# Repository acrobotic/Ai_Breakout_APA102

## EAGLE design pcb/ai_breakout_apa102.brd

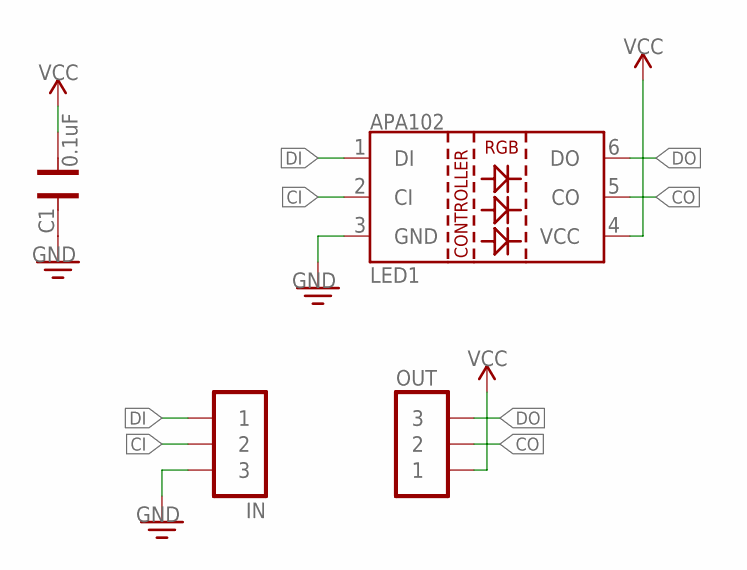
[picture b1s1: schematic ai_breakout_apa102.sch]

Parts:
C1: 0.1uF; CAP-0402
IN: 1X03
LED1: LED-APA102
OUT: 1X03NOFIRST; 1X03-NOFIRST

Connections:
CI: IN.2, LED1.2 (CI)
CO: LED1.5 (CO), OUT.2
DI: IN.1, LED1.1 (DI)
DO: LED1.6 (DO), OUT.3
GND: C1.2, IN.3, LED1.3 (GND)
VCC: C1.1, LED1.4 (VCC), OUT.1

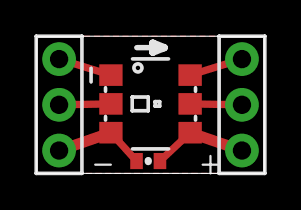
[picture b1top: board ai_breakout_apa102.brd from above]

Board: 2 copper layers, 12.7 x 7.6 mm, 5 parts (1 on the bottom side), 6 nets.

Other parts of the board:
U$5: AI-LOGO-XS

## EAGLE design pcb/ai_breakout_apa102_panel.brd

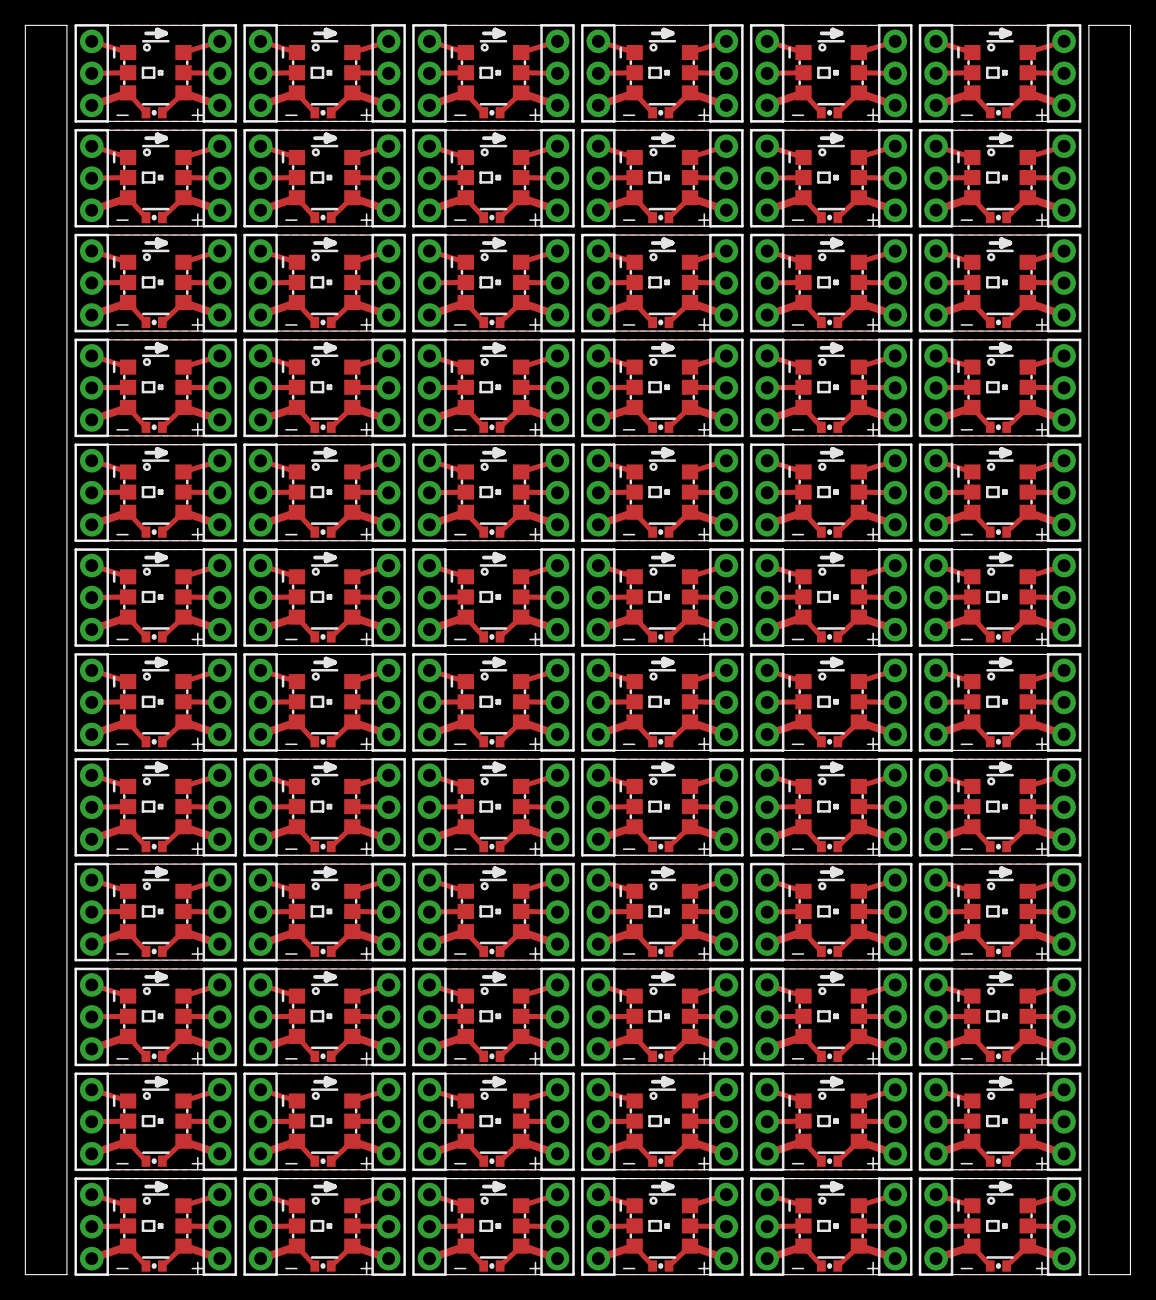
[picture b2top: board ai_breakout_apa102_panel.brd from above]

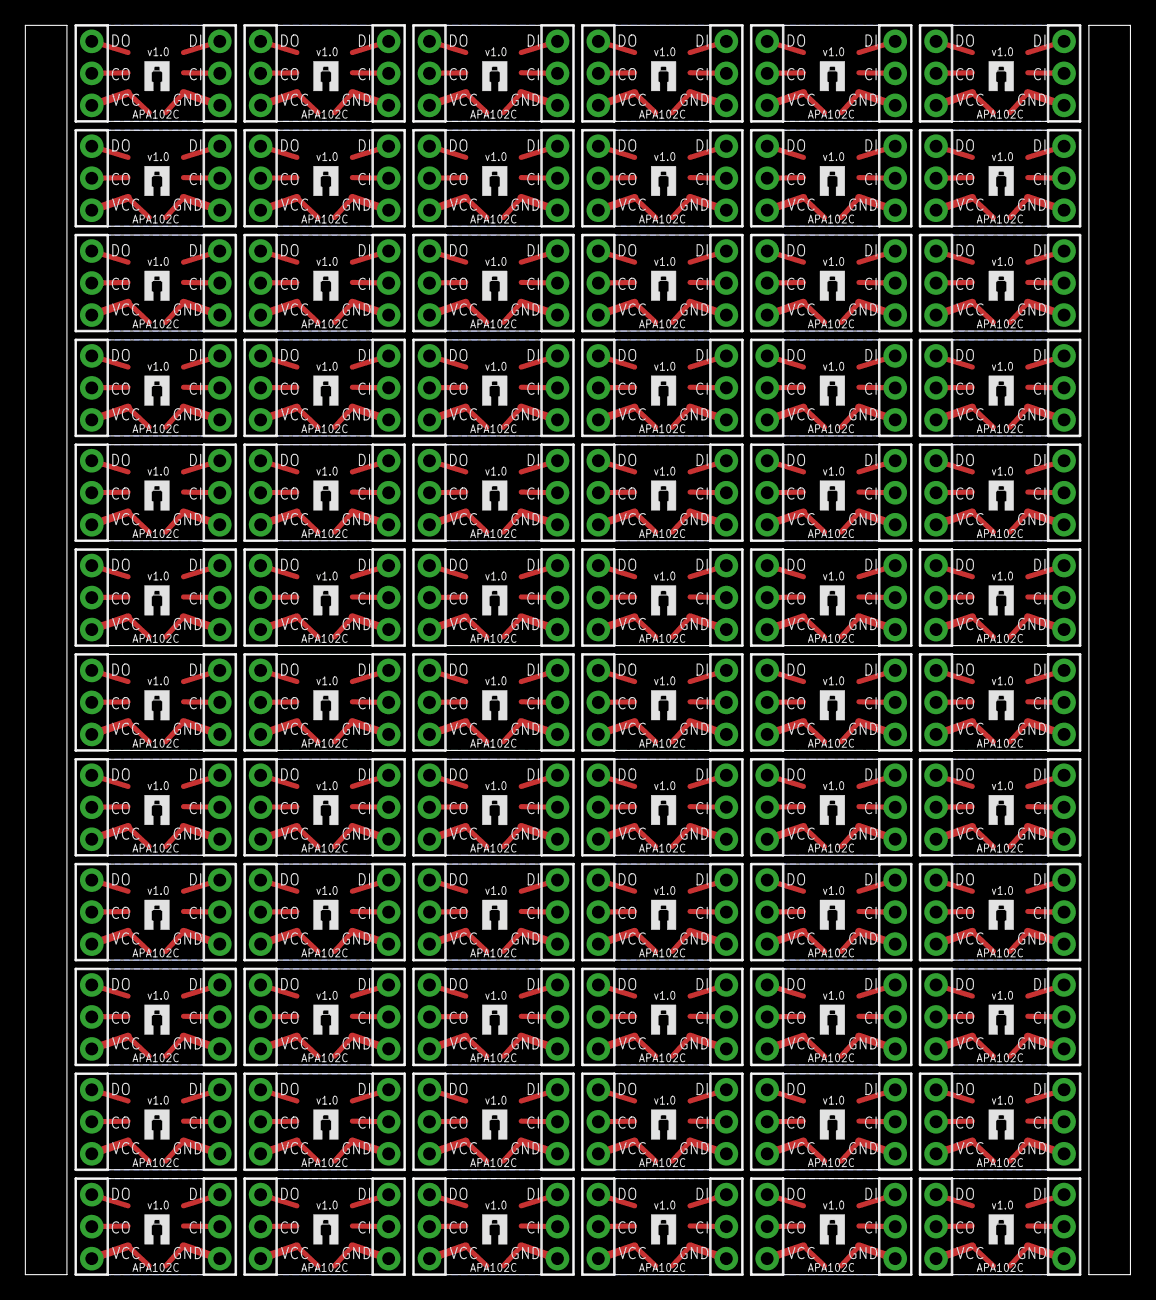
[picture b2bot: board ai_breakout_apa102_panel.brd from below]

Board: 2 copper layers, 87.7 x 99.1 mm, 360 parts (72 on the bottom side), 432 nets.

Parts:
C1, C2, C3, C4, C5, C6, C7, C8, C9, C10, C11, C12, C13, C14, C15, C16, C17, C18, C19, C20, C21, C22, C23, C24, C25, C26, C27, C28, C29, C30, C31, C32, C33, C34, C35, C36, C37, C38, C39, C40, C41, C42, C43, C44, C45, C46, C47, C48, C49, C50, C51, C52, C53, C54, C55, C56, C57, C58, C59, C60, C61, C62, C63, C64, C65, C66, C67, C68, C69, C70, C71, C72: 0.1uF; CAP-0402
IN, IN1, IN2, IN3, IN4, IN5, IN6, IN7, IN8, IN9, IN10, IN11, IN12, IN13, IN14, IN15, IN16, IN17, IN18, IN19, IN20, IN21, IN22, IN23, IN24, IN25, IN26, IN27, IN28, IN29, IN30, IN31, IN32, IN33, IN34, IN35, IN36, IN37, IN38, IN39, IN40, IN41, IN42, IN43, IN44, IN45, IN46, IN47, IN48, IN49, IN50, IN51, IN52, IN53, IN54, IN55, IN56, IN57, IN58, IN59, IN60, IN61, IN62, IN63, IN64, IN65, IN66, IN67, IN68, IN69, IN70, IN71: 1X03
LED1, LED2, LED3, LED4, LED5, LED6, LED7, LED8, LED9, LED10, LED11, LED12, LED13, LED14, LED15, LED16, LED17, LED18, LED19, LED20, LED21, LED22, LED23, LED24, LED25, LED26, LED27, LED28, LED29, LED30, LED31, LED32, LED33, LED34, LED35, LED36, LED37, LED38, LED39, LED40, LED41, LED42, LED43, LED44, LED45, LED46, LED47, LED48, LED49, LED50, LED51, LED52, LED53, LED54, LED55, LED56, LED57, LED58, LED59, LED60, LED61, LED62, LED63, LED64, LED65, LED66, LED67, LED68, LED69, LED70, LED71, LED72: LED-APA102
OUT, OUT1, OUT2, OUT3, OUT4, OUT5, OUT6, OUT7, OUT8, OUT9, OUT10, OUT11, OUT12, OUT13, OUT14, OUT15, OUT16, OUT17, OUT18, OUT19, OUT20, OUT21, OUT22, OUT23, OUT24, OUT25, OUT26, OUT27, OUT28, OUT29, OUT30, OUT31, OUT32, OUT33, OUT34, OUT35, OUT36, OUT37, OUT38, OUT39, OUT40, OUT41, OUT42, OUT43, OUT44, OUT45, OUT46, OUT47, OUT48, OUT49, OUT50, OUT51, OUT52, OUT53, OUT54, OUT55, OUT56, OUT57, OUT58, OUT59, OUT60, OUT61, OUT62, OUT63, OUT64, OUT65, OUT66, OUT67, OUT68, OUT69, OUT70, OUT71: 1X03NOFIRST; 1X03-NOFIRST
U$1, U$2, U$3, U$4, U$5, U$6, U$7, U$8, U$9, U$10, U$11, U$12, U$13, U$14, U$15, U$16, U$17, U$18, U$19, U$20, U$21, U$22, U$23, U$24, U$25, U$26, U$27, U$28, U$29, U$30, U$31, U$32, U$33, U$34, U$35, U$36, U$37, U$38, U$39, U$40, U$41, U$42, U$43, U$44, U$45, U$46, U$47, U$48, U$49, U$50, U$51, U$52, U$53, U$54, U$55, U$56, U$57, U$58, U$59, U$60, U$61, U$62, U$63, U$64, U$65, U$66, U$67, U$68, U$69, U$70, U$71, U$72: AI-LOGO-XS

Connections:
CI: IN.2, LED1.2
CI1: IN1.2, LED2.2
CI2: IN2.2, LED3.2
CI3: IN3.2, LED4.2
CI4: IN4.2, LED5.2
CI5: IN5.2, LED6.2
CI6: IN6.2, LED7.2
CI7: IN7.2, LED8.2
CI8: IN8.2, LED9.2
CI9: IN9.2, LED10.2
CI10: IN10.2, LED11.2
CI11: IN11.2, LED12.2
CI12: IN12.2, LED13.2
CI13: IN13.2, LED14.2
CI14: IN14.2, LED15.2
CI15: IN15.2, LED16.2
CI16: IN16.2, LED17.2
CI17: IN17.2, LED18.2
CI18: IN18.2, LED19.2
CI19: IN19.2, LED20.2
CI20: IN20.2, LED21.2
CI21: IN21.2, LED22.2
CI22: IN22.2, LED23.2
CI23: IN23.2, LED24.2
CI24: IN24.2, LED25.2
CI25: IN25.2, LED26.2
CI26: IN26.2, LED27.2
CI27: IN27.2, LED28.2
CI28: IN28.2, LED29.2
CI29: IN29.2, LED30.2
CI30: IN30.2, LED31.2
CI31: IN31.2, LED32.2
CI32: IN32.2, LED33.2
CI33: IN33.2, LED34.2
CI34: IN34.2, LED35.2
CI35: IN35.2, LED36.2
CI36: IN36.2, LED37.2
CI37: IN37.2, LED38.2
CI38: IN38.2, LED39.2
CI39: IN39.2, LED40.2
CI40: IN40.2, LED41.2
CI41: IN41.2, LED42.2
CI42: IN42.2, LED43.2
CI43: IN43.2, LED44.2
CI44: IN44.2, LED45.2
CI45: IN45.2, LED46.2
CI46: IN46.2, LED47.2
CI47: IN47.2, LED48.2
CI48: IN48.2, LED49.2
CI49: IN49.2, LED50.2
CI50: IN50.2, LED51.2
CI51: IN51.2, LED52.2
CI52: IN52.2, LED53.2
CI53: IN53.2, LED54.2
CI54: IN54.2, LED55.2
CI55: IN55.2, LED56.2
CI56: IN56.2, LED57.2
CI57: IN57.2, LED58.2
CI58: IN58.2, LED59.2
CI59: IN59.2, LED60.2
CI60: IN60.2, LED61.2
CI61: IN61.2, LED62.2
CI62: IN62.2, LED63.2
CI63: IN63.2, LED64.2
CI64: IN64.2, LED65.2
CI65: IN65.2, LED66.2
CI66: IN66.2, LED67.2
CI67: IN67.2, LED68.2
CI68: IN68.2, LED69.2
CI69: IN69.2, LED70.2
CI70: IN70.2, LED71.2
CI71: IN71.2, LED72.2
CO: LED1.5, OUT.2
CO1: LED2.5, OUT1.2
CO2: LED3.5, OUT2.2
CO3: LED4.5, OUT3.2
CO4: LED5.5, OUT4.2
CO5: LED6.5, OUT5.2
CO6: LED7.5, OUT6.2
CO7: LED8.5, OUT7.2
CO8: LED9.5, OUT8.2
CO9: LED10.5, OUT9.2
CO10: LED11.5, OUT10.2
CO11: LED12.5, OUT11.2
CO12: LED13.5, OUT12.2
CO13: LED14.5, OUT13.2
CO14: LED15.5, OUT14.2
CO15: LED16.5, OUT15.2
CO16: LED17.5, OUT16.2
CO17: LED18.5, OUT17.2
CO18: LED19.5, OUT18.2
CO19: LED20.5, OUT19.2
CO20: LED21.5, OUT20.2
CO21: LED22.5, OUT21.2
CO22: LED23.5, OUT22.2
CO23: LED24.5, OUT23.2
CO24: LED25.5, OUT24.2
CO25: LED26.5, OUT25.2
CO26: LED27.5, OUT26.2
CO27: LED28.5, OUT27.2
CO28: LED29.5, OUT28.2
CO29: LED30.5, OUT29.2
CO30: LED31.5, OUT30.2
CO31: LED32.5, OUT31.2
CO32: LED33.5, OUT32.2
CO33: LED34.5, OUT33.2
CO34: LED35.5, OUT34.2
CO35: LED36.5, OUT35.2
CO36: LED37.5, OUT36.2
CO37: LED38.5, OUT37.2
CO38: LED39.5, OUT38.2
CO39: LED40.5, OUT39.2
CO40: LED41.5, OUT40.2
CO41: LED42.5, OUT41.2
CO42: LED43.5, OUT42.2
CO43: LED44.5, OUT43.2
CO44: LED45.5, OUT44.2
CO45: LED46.5, OUT45.2
CO46: LED47.5, OUT46.2
CO47: LED48.5, OUT47.2
CO48: LED49.5, OUT48.2
CO49: LED50.5, OUT49.2
CO50: LED51.5, OUT50.2
CO51: LED52.5, OUT51.2
CO52: LED53.5, OUT52.2
CO53: LED54.5, OUT53.2
CO54: LED55.5, OUT54.2
CO55: LED56.5, OUT55.2
CO56: LED57.5, OUT56.2
CO57: LED58.5, OUT57.2
CO58: LED59.5, OUT58.2
CO59: LED60.5, OUT59.2
CO60: LED61.5, OUT60.2
CO61: LED62.5, OUT61.2
CO62: LED63.5, OUT62.2
CO63: LED64.5, OUT63.2
CO64: LED65.5, OUT64.2
CO65: LED66.5, OUT65.2
CO66: LED67.5, OUT66.2
CO67: LED68.5, OUT67.2
CO68: LED69.5, OUT68.2
CO69: LED70.5, OUT69.2
CO70: LED71.5, OUT70.2
CO71: LED72.5, OUT71.2
DI: IN.1, LED1.1
DI1: IN1.1, LED2.1
DI2: IN2.1, LED3.1
DI3: IN3.1, LED4.1
DI4: IN4.1, LED5.1
DI5: IN5.1, LED6.1
DI6: IN6.1, LED7.1
DI7: IN7.1, LED8.1
DI8: IN8.1, LED9.1
DI9: IN9.1, LED10.1
DI10: IN10.1, LED11.1
DI11: IN11.1, LED12.1
DI12: IN12.1, LED13.1
DI13: IN13.1, LED14.1
DI14: IN14.1, LED15.1
DI15: IN15.1, LED16.1
DI16: IN16.1, LED17.1
DI17: IN17.1, LED18.1
DI18: IN18.1, LED19.1
DI19: IN19.1, LED20.1
DI20: IN20.1, LED21.1
DI21: IN21.1, LED22.1
DI22: IN22.1, LED23.1
DI23: IN23.1, LED24.1
DI24: IN24.1, LED25.1
DI25: IN25.1, LED26.1
DI26: IN26.1, LED27.1
DI27: IN27.1, LED28.1
DI28: IN28.1, LED29.1
DI29: IN29.1, LED30.1
DI30: IN30.1, LED31.1
DI31: IN31.1, LED32.1
DI32: IN32.1, LED33.1
DI33: IN33.1, LED34.1
DI34: IN34.1, LED35.1
DI35: IN35.1, LED36.1
DI36: IN36.1, LED37.1
DI37: IN37.1, LED38.1
DI38: IN38.1, LED39.1
DI39: IN39.1, LED40.1
DI40: IN40.1, LED41.1
DI41: IN41.1, LED42.1
DI42: IN42.1, LED43.1
DI43: IN43.1, LED44.1
DI44: IN44.1, LED45.1
DI45: IN45.1, LED46.1
DI46: IN46.1, LED47.1
DI47: IN47.1, LED48.1
DI48: IN48.1, LED49.1
DI49: IN49.1, LED50.1
DI50: IN50.1, LED51.1
DI51: IN51.1, LED52.1
DI52: IN52.1, LED53.1
DI53: IN53.1, LED54.1
DI54: IN54.1, LED55.1
DI55: IN55.1, LED56.1
DI56: IN56.1, LED57.1
DI57: IN57.1, LED58.1
DI58: IN58.1, LED59.1
DI59: IN59.1, LED60.1
DI60: IN60.1, LED61.1
DI61: IN61.1, LED62.1
DI62: IN62.1, LED63.1
DI63: IN63.1, LED64.1
DI64: IN64.1, LED65.1
DI65: IN65.1, LED66.1
DI66: IN66.1, LED67.1
DI67: IN67.1, LED68.1
DI68: IN68.1, LED69.1
DI69: IN69.1, LED70.1
DI70: IN70.1, LED71.1
DI71: IN71.1, LED72.1
DO: LED1.6, OUT.3
DO1: LED2.6, OUT1.3
DO2: LED3.6, OUT2.3
DO3: LED4.6, OUT3.3
DO4: LED5.6, OUT4.3
DO5: LED6.6, OUT5.3
DO6: LED7.6, OUT6.3
DO7: LED8.6, OUT7.3
DO8: LED9.6, OUT8.3
DO9: LED10.6, OUT9.3
DO10: LED11.6, OUT10.3
DO11: LED12.6, OUT11.3
DO12: LED13.6, OUT12.3
DO13: LED14.6, OUT13.3
DO14: LED15.6, OUT14.3
DO15: LED16.6, OUT15.3
DO16: LED17.6, OUT16.3
DO17: LED18.6, OUT17.3
DO18: LED19.6, OUT18.3
DO19: LED20.6, OUT19.3
DO20: LED21.6, OUT20.3
DO21: LED22.6, OUT21.3
DO22: LED23.6, OUT22.3
DO23: LED24.6, OUT23.3
DO24: LED25.6, OUT24.3
DO25: LED26.6, OUT25.3
DO26: LED27.6, OUT26.3
DO27: LED28.6, OUT27.3
DO28: LED29.6, OUT28.3
DO29: LED30.6, OUT29.3
DO30: LED31.6, OUT30.3
DO31: LED32.6, OUT31.3
DO32: LED33.6, OUT32.3
DO33: LED34.6, OUT33.3
DO34: LED35.6, OUT34.3
DO35: LED36.6, OUT35.3
DO36: LED37.6, OUT36.3
DO37: LED38.6, OUT37.3
DO38: LED39.6, OUT38.3
DO39: LED40.6, OUT39.3
DO40: LED41.6, OUT40.3
DO41: LED42.6, OUT41.3
DO42: LED43.6, OUT42.3
DO43: LED44.6, OUT43.3
DO44: LED45.6, OUT44.3
DO45: LED46.6, OUT45.3
DO46: LED47.6, OUT46.3
DO47: LED48.6, OUT47.3
DO48: LED49.6, OUT48.3
DO49: LED50.6, OUT49.3
DO50: LED51.6, OUT50.3
DO51: LED52.6, OUT51.3
DO52: LED53.6, OUT52.3
DO53: LED54.6, OUT53.3
DO54: LED55.6, OUT54.3
DO55: LED56.6, OUT55.3
DO56: LED57.6, OUT56.3
DO57: LED58.6, OUT57.3
DO58: LED59.6, OUT58.3
DO59: LED60.6, OUT59.3
DO60: LED61.6, OUT60.3
DO61: LED62.6, OUT61.3
DO62: LED63.6, OUT62.3
DO63: LED64.6, OUT63.3
DO64: LED65.6, OUT64.3
DO65: LED66.6, OUT65.3
DO66: LED67.6, OUT66.3
DO67: LED68.6, OUT67.3
DO68: LED69.6, OUT68.3
DO69: LED70.6, OUT69.3
DO70: LED71.6, OUT70.3
DO71: LED72.6, OUT71.3
GND: C1.2, IN.3, LED1.3
GND1: C2.2, IN1.3, LED2.3
GND2: C3.2, IN2.3, LED3.3
GND3: C4.2, IN3.3, LED4.3
GND4: C5.2, IN4.3, LED5.3
GND5: C6.2, IN5.3, LED6.3
GND6: C7.2, IN6.3, LED7.3
GND7: C8.2, IN7.3, LED8.3
GND8: C9.2, IN8.3, LED9.3
GND9: C10.2, IN9.3, LED10.3
GND10: C11.2, IN10.3, LED11.3
GND11: C12.2, IN11.3, LED12.3
GND12: C13.2, IN12.3, LED13.3
GND13: C14.2, IN13.3, LED14.3
GND14: C15.2, IN14.3, LED15.3
GND15: C16.2, IN15.3, LED16.3
GND16: C17.2, IN16.3, LED17.3
GND17: C18.2, IN17.3, LED18.3
GND18: C19.2, IN18.3, LED19.3
GND19: C20.2, IN19.3, LED20.3
GND20: C21.2, IN20.3, LED21.3
GND21: C22.2, IN21.3, LED22.3
GND22: C23.2, IN22.3, LED23.3
GND23: C24.2, IN23.3, LED24.3
GND24: C25.2, IN24.3, LED25.3
GND25: C26.2, IN25.3, LED26.3
GND26: C27.2, IN26.3, LED27.3
GND27: C28.2, IN27.3, LED28.3
GND28: C29.2, IN28.3, LED29.3
GND29: C30.2, IN29.3, LED30.3
GND30: C31.2, IN30.3, LED31.3
GND31: C32.2, IN31.3, LED32.3
GND32: C33.2, IN32.3, LED33.3
GND33: C34.2, IN33.3, LED34.3
GND34: C35.2, IN34.3, LED35.3
GND35: C36.2, IN35.3, LED36.3
GND36: C37.2, IN36.3, LED37.3
GND37: C38.2, IN37.3, LED38.3
GND38: C39.2, IN38.3, LED39.3
GND39: C40.2, IN39.3, LED40.3
GND40: C41.2, IN40.3, LED41.3
GND41: C42.2, IN41.3, LED42.3
GND42: C43.2, IN42.3, LED43.3
GND43: C44.2, IN43.3, LED44.3
GND44: C45.2, IN44.3, LED45.3
GND45: C46.2, IN45.3, LED46.3
GND46: C47.2, IN46.3, LED47.3
GND47: C48.2, IN47.3, LED48.3
GND48: C49.2, IN48.3, LED49.3
GND49: C50.2, IN49.3, LED50.3
GND50: C51.2, IN50.3, LED51.3
GND51: C52.2, IN51.3, LED52.3
GND52: C53.2, IN52.3, LED53.3
GND53: C54.2, IN53.3, LED54.3
GND54: C55.2, IN54.3, LED55.3
GND55: C56.2, IN55.3, LED56.3
GND56: C57.2, IN56.3, LED57.3
GND57: C58.2, IN57.3, LED58.3
GND58: C59.2, IN58.3, LED59.3
GND59: C60.2, IN59.3, LED60.3
GND60: C61.2, IN60.3, LED61.3
GND61: C62.2, IN61.3, LED62.3
GND62: C63.2, IN62.3, LED63.3
GND63: C64.2, IN63.3, LED64.3
GND64: C65.2, IN64.3, LED65.3
GND65: C66.2, IN65.3, LED66.3
GND66: C67.2, IN66.3, LED67.3
GND67: C68.2, IN67.3, LED68.3
GND68: C69.2, IN68.3, LED69.3
GND69: C70.2, IN69.3, LED70.3
GND70: C71.2, IN70.3, LED71.3
GND71: C72.2, IN71.3, LED72.3
VCC: C1.1, LED1.4, OUT.1
VCC1: C2.1, LED2.4, OUT1.1
VCC2: C3.1, LED3.4, OUT2.1
VCC3: C4.1, LED4.4, OUT3.1
VCC4: C5.1, LED5.4, OUT4.1
VCC5: C6.1, LED6.4, OUT5.1
VCC6: C7.1, LED7.4, OUT6.1
VCC7: C8.1, LED8.4, OUT7.1
VCC8: C9.1, LED9.4, OUT8.1
VCC9: C10.1, LED10.4, OUT9.1
VCC10: C11.1, LED11.4, OUT10.1
VCC11: C12.1, LED12.4, OUT11.1
VCC12: C13.1, LED13.4, OUT12.1
VCC13: C14.1, LED14.4, OUT13.1
VCC14: C15.1, LED15.4, OUT14.1
VCC15: C16.1, LED16.4, OUT15.1
VCC16: C17.1, LED17.4, OUT16.1
VCC17: C18.1, LED18.4, OUT17.1
VCC18: C19.1, LED19.4, OUT18.1
VCC19: C20.1, LED20.4, OUT19.1
VCC20: C21.1, LED21.4, OUT20.1
VCC21: C22.1, LED22.4, OUT21.1
VCC22: C23.1, LED23.4, OUT22.1
VCC23: C24.1, LED24.4, OUT23.1
VCC24: C25.1, LED25.4, OUT24.1
VCC25: C26.1, LED26.4, OUT25.1
VCC26: C27.1, LED27.4, OUT26.1
VCC27: C28.1, LED28.4, OUT27.1
VCC28: C29.1, LED29.4, OUT28.1
VCC29: C30.1, LED30.4, OUT29.1
VCC30: C31.1, LED31.4, OUT30.1
VCC31: C32.1, LED32.4, OUT31.1
VCC32: C33.1, LED33.4, OUT32.1
VCC33: C34.1, LED34.4, OUT33.1
VCC34: C35.1, LED35.4, OUT34.1
VCC35: C36.1, LED36.4, OUT35.1
VCC36: C37.1, LED37.4, OUT36.1
VCC37: C38.1, LED38.4, OUT37.1
VCC38: C39.1, LED39.4, OUT38.1
VCC39: C40.1, LED40.4, OUT39.1
VCC40: C41.1, LED41.4, OUT40.1
VCC41: C42.1, LED42.4, OUT41.1
VCC42: C43.1, LED43.4, OUT42.1
VCC43: C44.1, LED44.4, OUT43.1
VCC44: C45.1, LED45.4, OUT44.1
VCC45: C46.1, LED46.4, OUT45.1
VCC46: C47.1, LED47.4, OUT46.1
VCC47: C48.1, LED48.4, OUT47.1
VCC48: C49.1, LED49.4, OUT48.1
VCC49: C50.1, LED50.4, OUT49.1
VCC50: C51.1, LED51.4, OUT50.1
VCC51: C52.1, LED52.4, OUT51.1
VCC52: C53.1, LED53.4, OUT52.1
VCC53: C54.1, LED54.4, OUT53.1
VCC54: C55.1, LED55.4, OUT54.1
VCC55: C56.1, LED56.4, OUT55.1
VCC56: C57.1, LED57.4, OUT56.1
VCC57: C58.1, LED58.4, OUT57.1
VCC58: C59.1, LED59.4, OUT58.1
VCC59: C60.1, LED60.4, OUT59.1
VCC60: C61.1, LED61.4, OUT60.1
VCC61: C62.1, LED62.4, OUT61.1
VCC62: C63.1, LED63.4, OUT62.1
VCC63: C64.1, LED64.4, OUT63.1
VCC64: C65.1, LED65.4, OUT64.1
VCC65: C66.1, LED66.4, OUT65.1
VCC66: C67.1, LED67.4, OUT66.1
VCC67: C68.1, LED68.4, OUT67.1
VCC68: C69.1, LED69.4, OUT68.1
VCC69: C70.1, LED70.4, OUT69.1
VCC70: C71.1, LED71.4, OUT70.1
VCC71: C72.1, LED72.4, OUT71.1

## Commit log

2015-02-26 first commit.
2015-02-26 adding panel
2015-02-27 Updating BOM
